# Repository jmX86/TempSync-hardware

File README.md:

# TempSync-hardware
Električne sheme i software za termostat

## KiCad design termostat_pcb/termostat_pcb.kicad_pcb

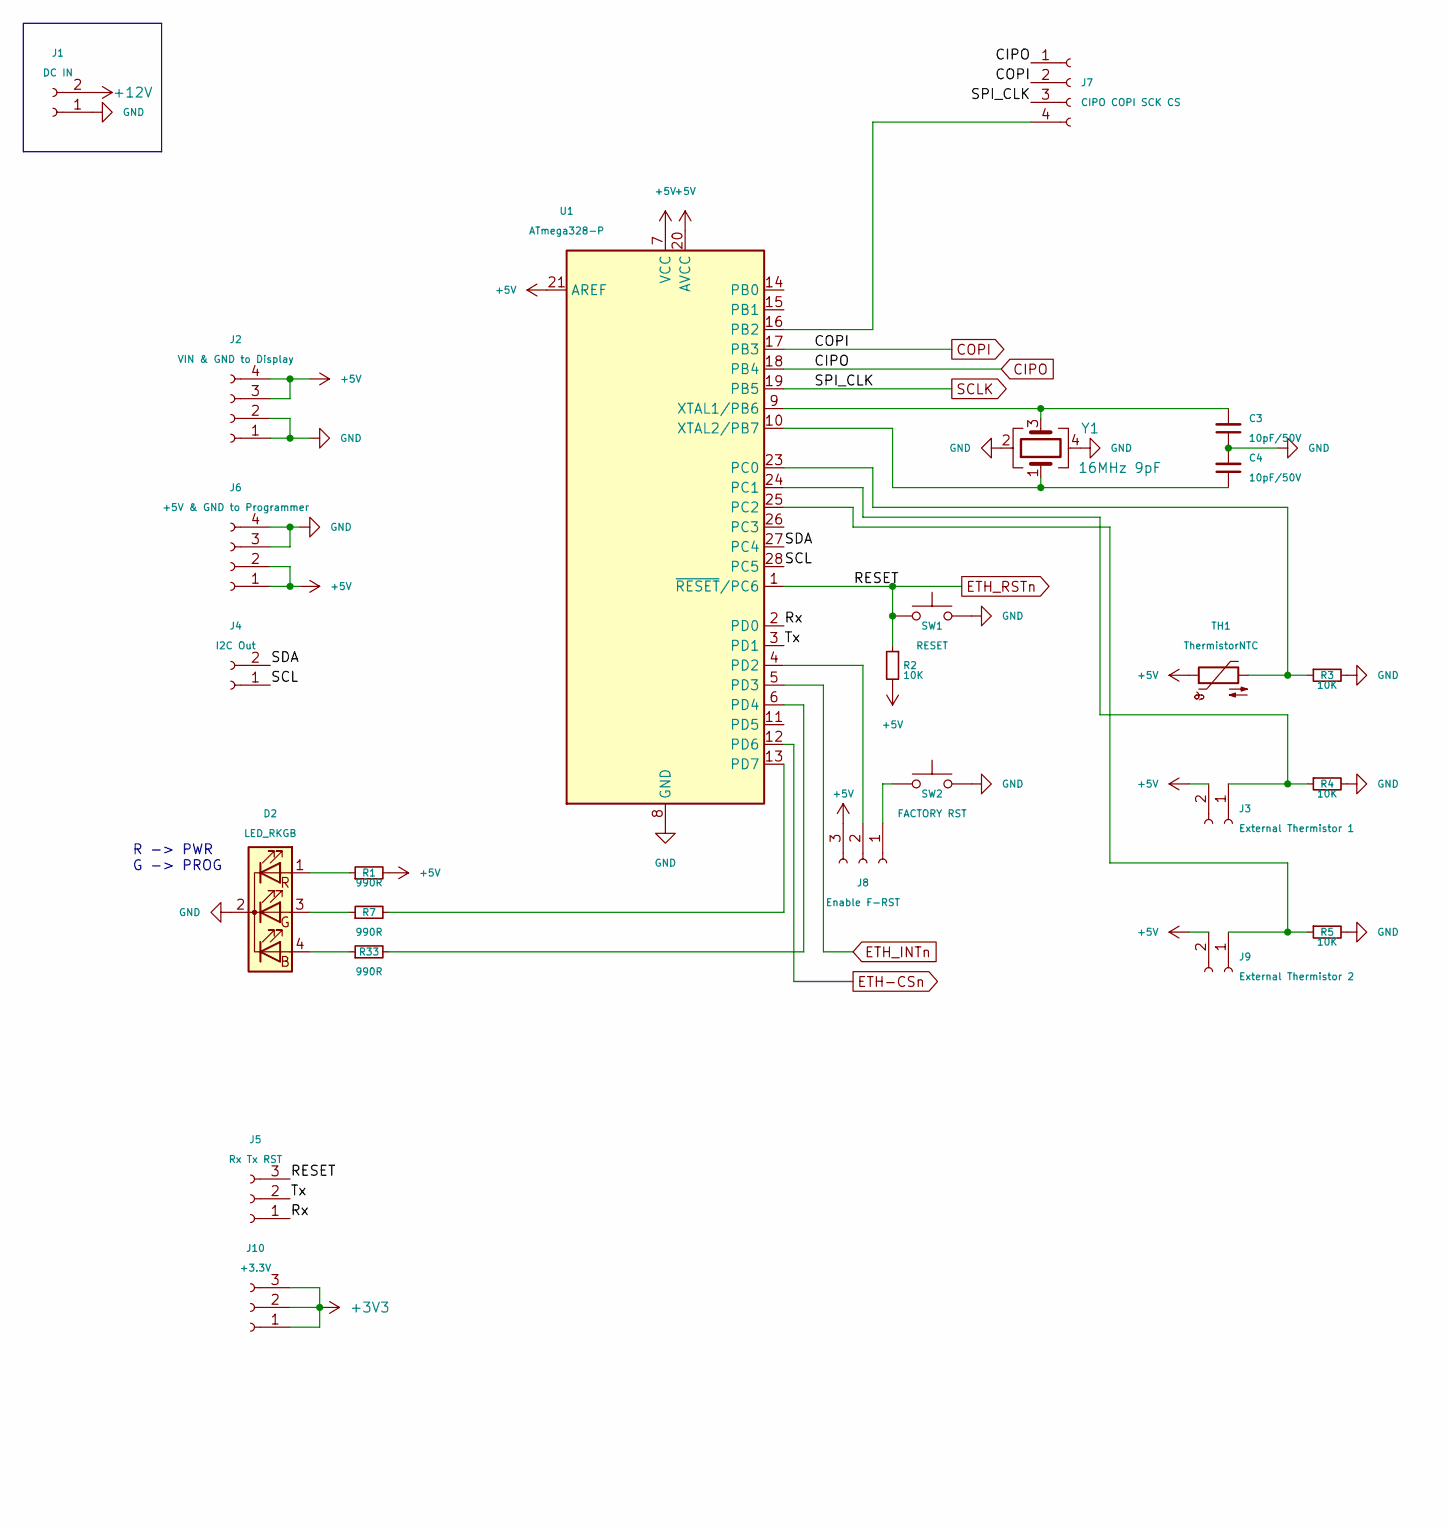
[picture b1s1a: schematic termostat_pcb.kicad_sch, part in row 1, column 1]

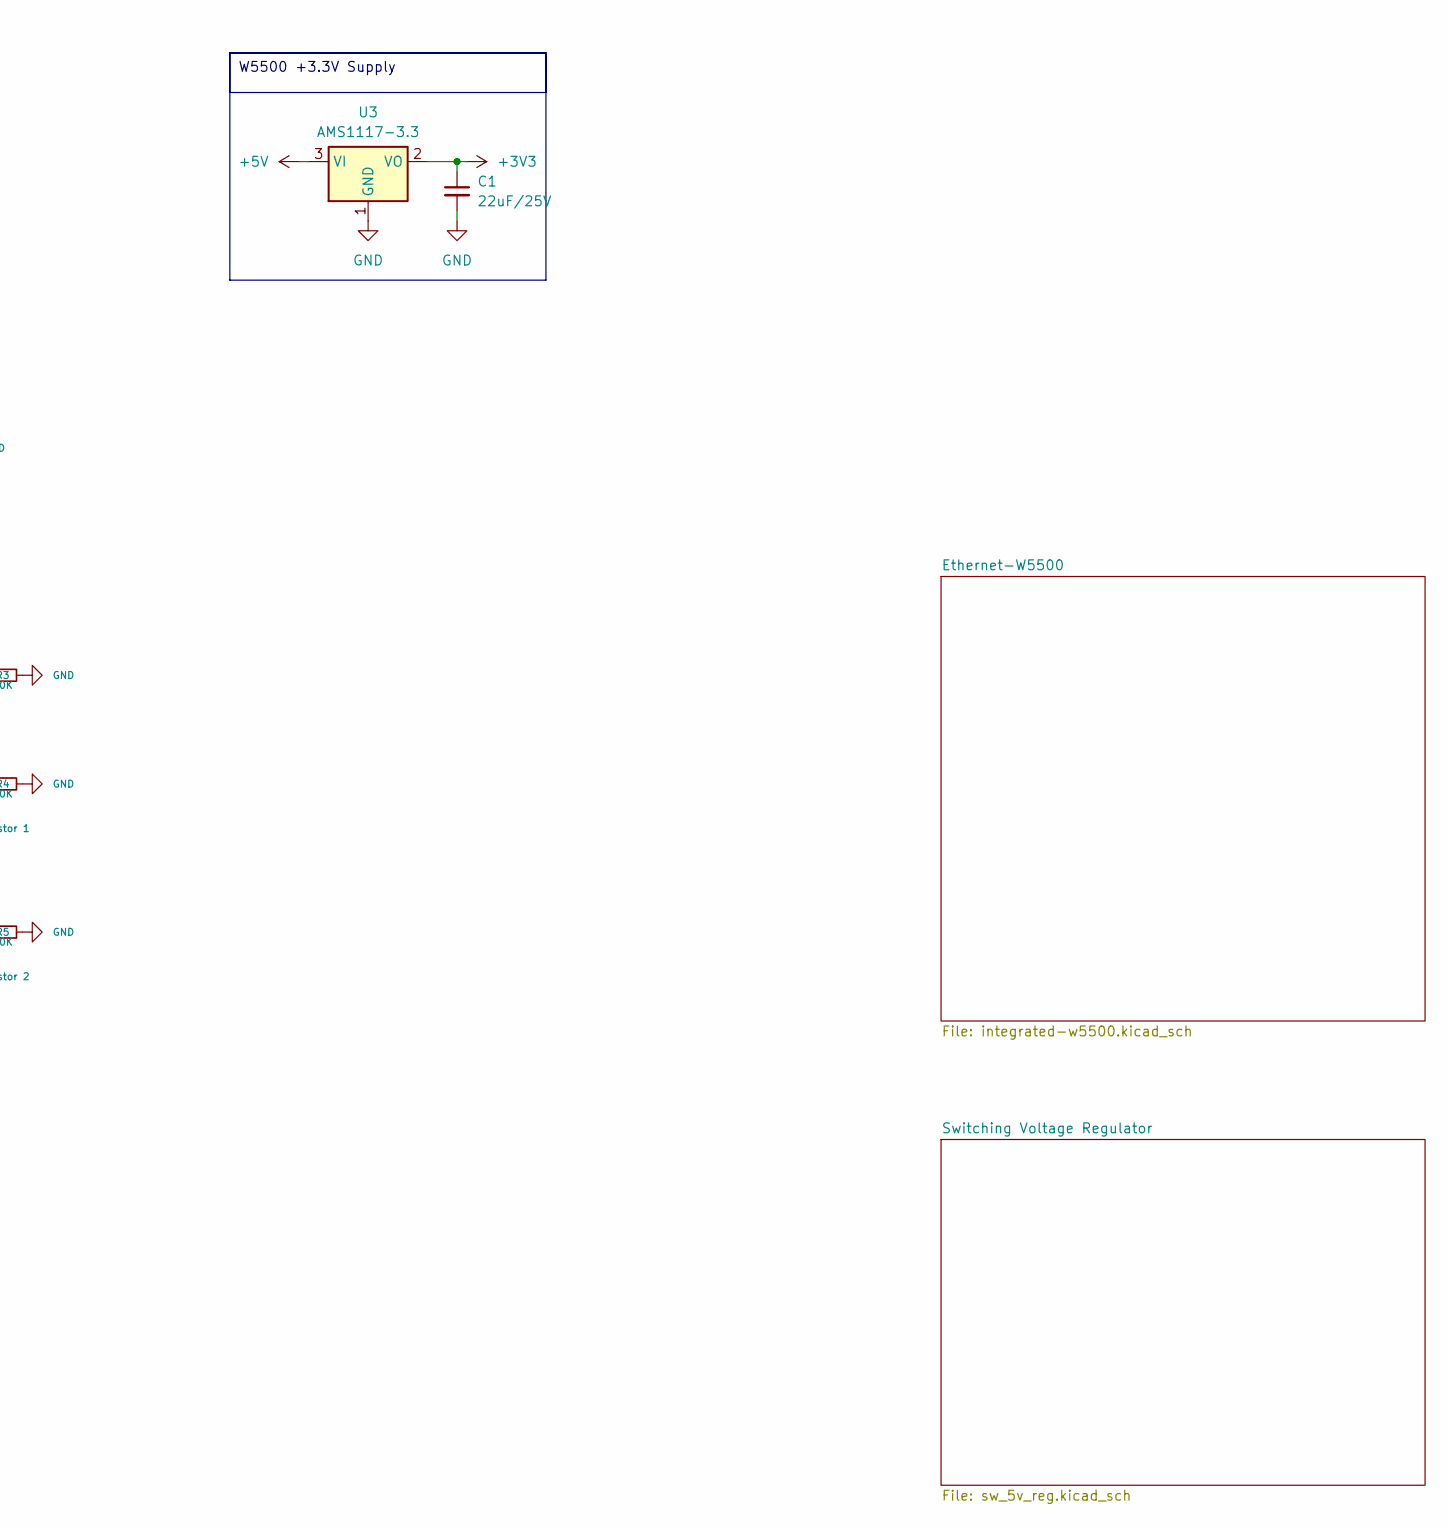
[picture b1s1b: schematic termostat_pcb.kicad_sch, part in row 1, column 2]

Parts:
C1: 22uF/25V; C_0805_2012Metric; LCSC C45783
C3, C4: 10pF/50V; C_0603_1608Metric; LCSC C1634
D2: LED_RKGB; LED_D5.0mm-4_RGB
J1: DC IN; PhoenixContact_MCV_1,5_2-G-5.08_1x02_P5.08mm_Vertical
J2: VIN & GND to Display; PinHeader_1x04_P2.54mm_Vertical
J3: External Thermistor 1; PhoenixContact_MCV_1,5_2-G-5.08_1x02_P5.08mm_Vertical
J4: I2C Out; PinHeader_1x02_P2.54mm_Vertical
J5: Rx Tx RST; PinHeader_1x03_P2.54mm_Vertical
J6: +5V & GND to Programmer; PinHeader_1x04_P2.54mm_Vertical
J7: CIPO COPI SCK CS; PinHeader_1x04_P2.54mm_Vertical
J8: Enable F-RST; PinHeader_1x03_P2.54mm_Vertical
J9: External Thermistor 2; PhoenixContact_MCV_1,5_2-G-5.08_1x02_P5.08mm_Vertical
J10: +3.3V; PinHeader_1x03_P2.54mm_Vertical
R1, R7, R33: 990R; R_Axial_DIN0207_L6.3mm_D2.5mm_P10.16mm_Horizontal
R2, R3, R4, R5: 10K; R_1206_3216Metric; LCSC C17902
SW1: RESET; SW_PUSH_6mm_H5mm
SW2: FACTORY RST; SW_PUSH_6mm_H5mm
TH1: ThermistorNTC; R_Axial_DIN0204_L3.6mm_D1.6mm_P1.90mm_Vertical
U1: ATmega328-P; DIP-28_W7.62mm
U3: AMS1117-3.3; SOT-223-3_TabPin2; LCSC C6186
Y1: 16MHz 9pF; Crystal_SMD_3225-4Pin_3.2x2.5mm; LCSC C13638

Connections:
+3V3: C1.1, J10.1, J10.2, J10.3, U3.2 (VO); also elsewhere on the board
+5V: J2.3, J2.4, J3.2, J6.1, J6.2, J8.3, J9.2, R1.2, R2.2, TH1.1, U1.7 (VCC), U1.20 (AVCC), U1.21 (AREF), U3.3 (VI); also elsewhere on the board
+12V: J1.2; also elsewhere on the board
/Rx: J5.1, U1.2 (PD0)
/SCL: J4.1, U1.28 (PC5)
/SDA: J4.2, U1.27 (PC4)
/Tx: J5.2, U1.3 (PD1)
CIPO: J7.1, U1.18 (PB4); also elsewhere on the board
COPI: J7.2, U1.17 (PB3); also elsewhere on the board
ETH-CSn: U1.12 (PD6); also elsewhere on the board
ETH_INTn: U1.5 (PD3); also elsewhere on the board
ETH_RSTn: J5.3, R2.1, SW1.1, U1.1 (~RESET/PC6); also elsewhere on the board
GND: C1.2, C3.1, C4.2, D2.2 (K), J1.1, J2.1, J2.2, J6.3, J6.4, R3.2, R4.2, R5.2, SW1.2, SW2.2, U1.8 (GND), U1.22 (GND), U3.1 (GND), Y1.2, Y1.4; also elsewhere on the board
unnamed: D2.4 (BA), R33.1
unnamed: D2.3 (GA), R7.1
unnamed: D2.1 (RA), R1.1
unnamed: J3.1, R4.1, U1.24 (PC1)
unnamed: J7.4, U1.16 (PB2)
unnamed: J8.1, SW2.1
unnamed: J8.2, U1.4 (PD2)
unnamed: J9.1, R5.1, U1.25 (PC2)
unnamed: R3.1, TH1.2, U1.23 (PC0)
unnamed: R33.2, U1.6 (PD4)
unnamed: R7.2, U1.13 (PD7)
unnamed: C3.2, U1.9 (XTAL1/PB6), Y1.3
unnamed: C4.1, U1.10 (XTAL2/PB7), Y1.1
SCLK: J7.3, U1.19 (PB5); also elsewhere on the board

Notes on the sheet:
W5500 +3.3V Supply
R -> PWR G -> PROG

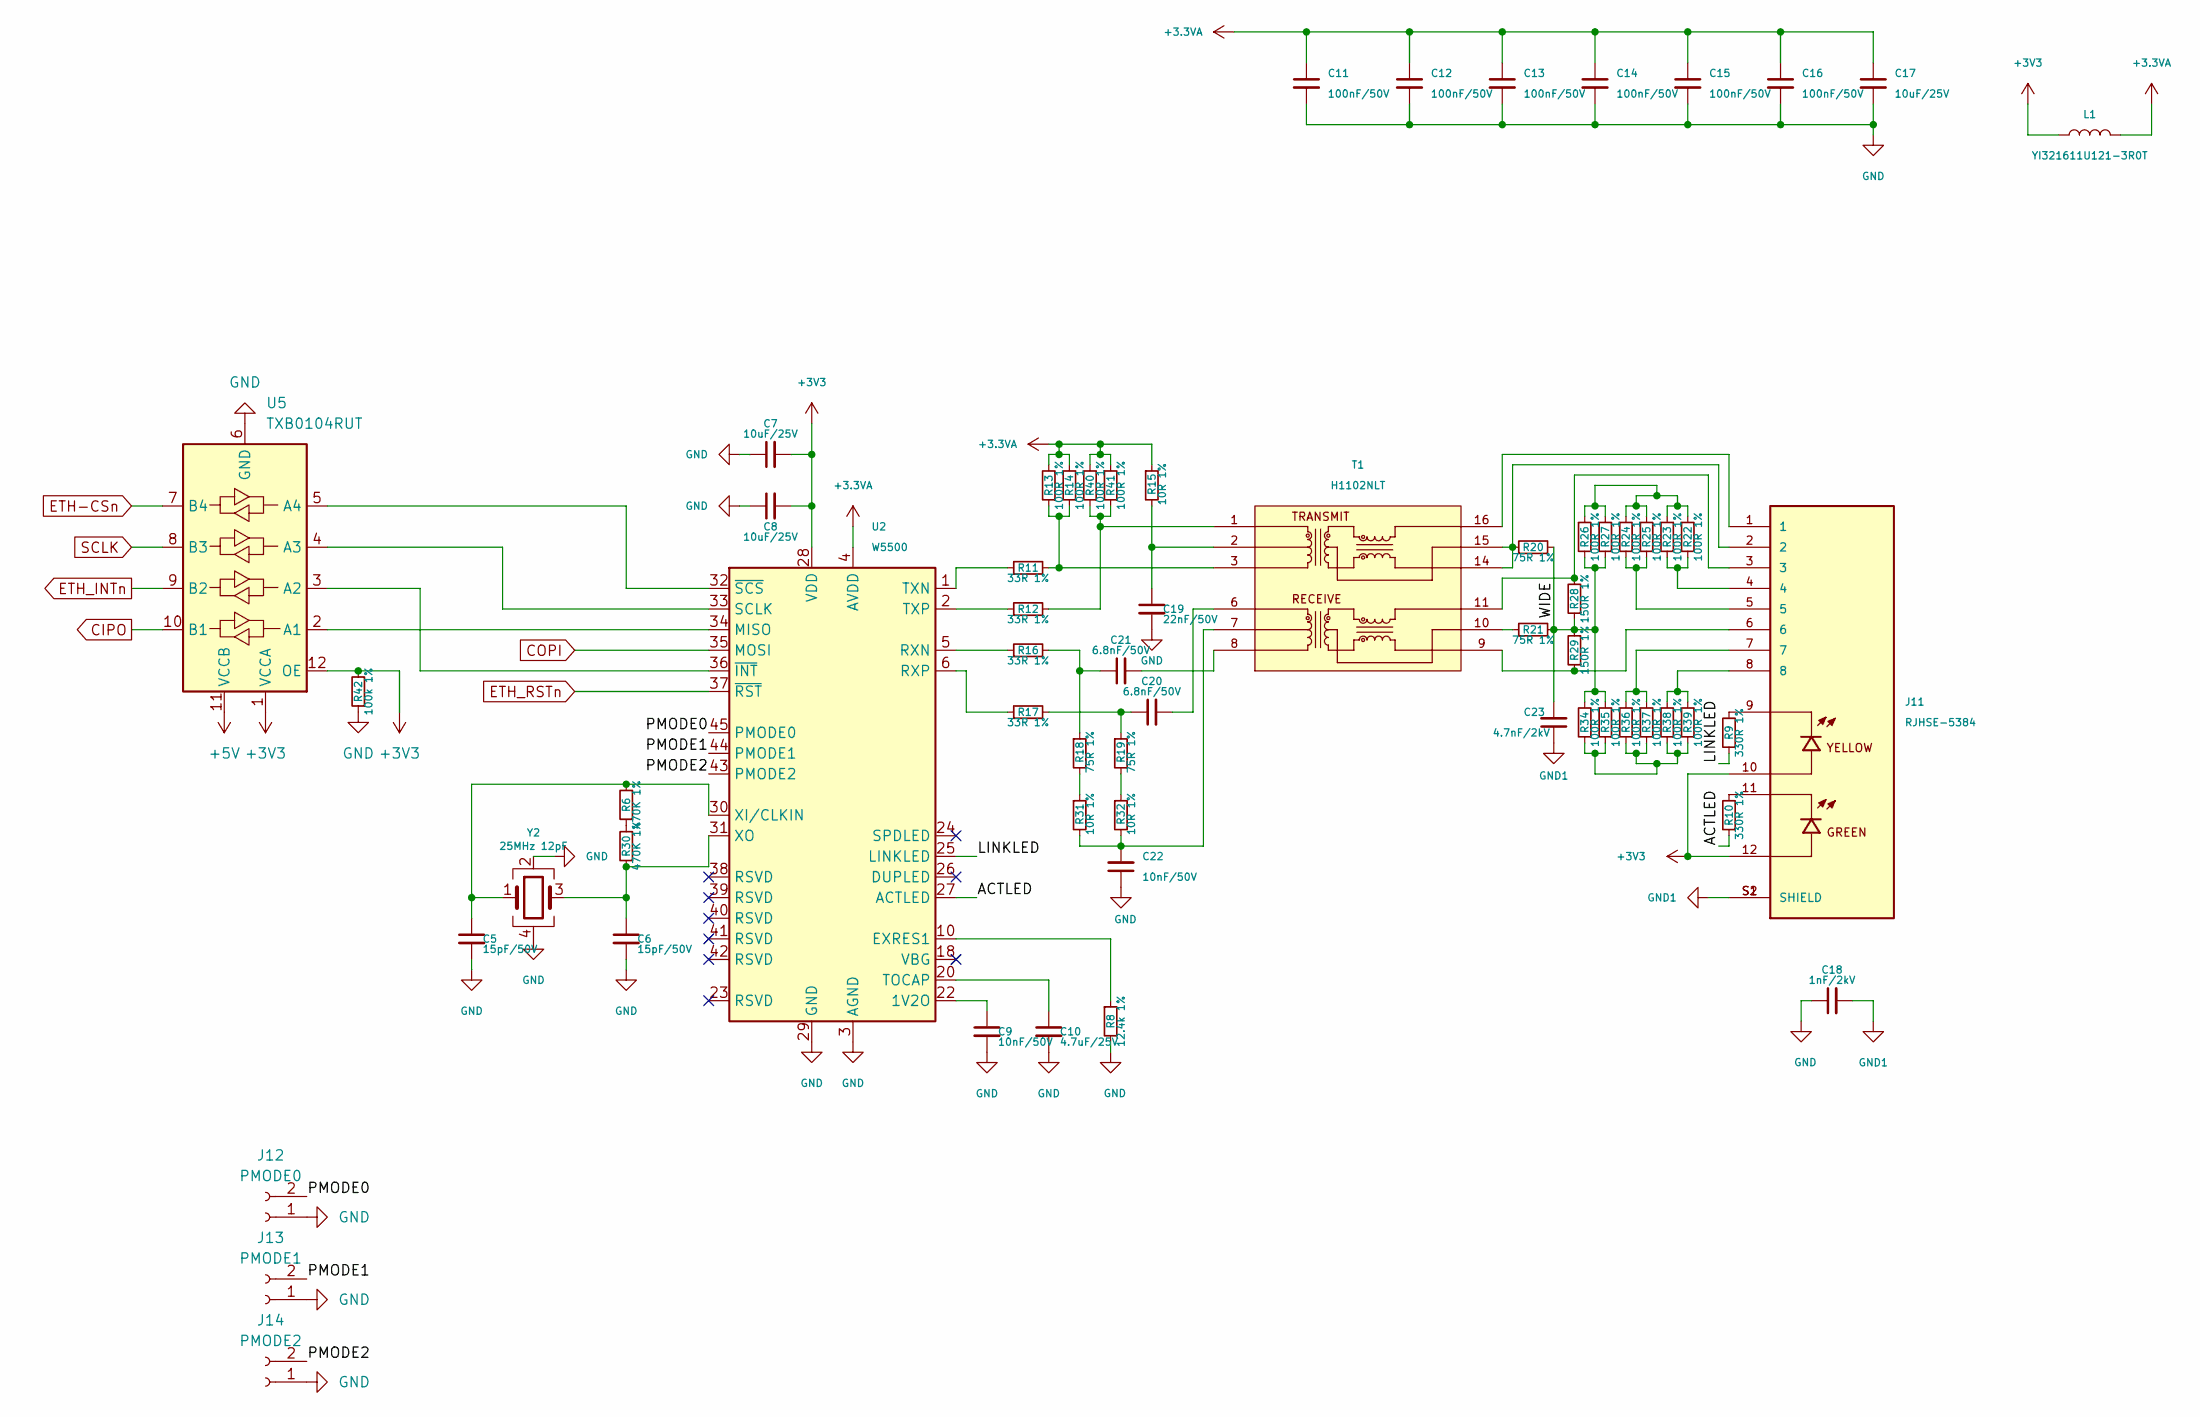
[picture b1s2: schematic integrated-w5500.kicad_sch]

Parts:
C5, C6: 15pF/50V; C_0603_1608Metric; LCSC C1644
C7, C8, C17: 10uF/25V; C_0805_2012Metric; LCSC C15850
C9, C22: 10nF/50V; C_0805_2012Metric; LCSC C1710
C10: 4.7uF/25V; C_0805_2012Metric; LCSC C1779
C11, C12, C13, C14, C15, C16: 100nF/50V; C_1206_3216Metric; LCSC C24497
C18: 1nF/2kV; C_1206_3216Metric; LCSC C9196
C19: 22nF/50V; C_0603_1608Metric; LCSC C21122
C20, C21: 6.8nF/50V; C_0603_1608Metric; LCSC C1631
C23: 4.7nF/2kV; C_1210_3225Metric; LCSC C427530
J11: RJHSE-5384; AMPHENOL_RJHSE-5384; PARTREV E; LCSC C464587
J12: PMODE0; PinHeader_1x02_P2.54mm_Vertical
J13: PMODE1; PinHeader_1x02_P2.54mm_Vertical
J14: PMODE2; PinHeader_1x02_P2.54mm_Vertical
L1: YI321611U121-3R0T; L_1206_3216Metric; LCSC C2858470
R6, R30: 470K 1%; R_0805_2012Metric; LCSC C17709
R8: 12.4k 1%; R_1206_3216Metric; LCSC C322840
R9, R10: 330R 1%; R_0805_2012Metric; LCSC C17630
R11, R12, R16, R17: 33R 1%; R_0805_2012Metric; LCSC C17634
R13, R14, R22, R23, R24, R25, R26, R27, R34, R35, R36, R37, R38, R39, R40, R41: 100R 1%; R_0805_2012Metric; LCSC C17408
R15, R31, R32: 10R 1%; R_1206_3216Metric; LCSC C17903
R18, R19, R20, R21: 75R 1%; R_0603_1608Metric; LCSC C4275
R28, R29: 150R 1%; R_0805_2012Metric; LCSC C17471
R42: 100k 1%; R_0603_1608Metric; LCSC C25803
T1: H1102NLT; XFMR_H1102NLT; PARTREV NA; LCSC C18584
U2: W5500; LQFP-48_7x7mm_P0.5mm; LCSC C32843
U5: TXB0104RUT; Texas_R-PUQFN-N12; LCSC C105266
Y2: 25MHz 12pF; Crystal_SMD_3225-4Pin_3.2x2.5mm; LCSC C9006

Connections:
+3.3VA: C11.1, C12.1, C13.1, C14.1, C15.1, C16.1, C17.1, L1.2, R13.2, R14.2, R15.1, R40.2, R41.2, U2.4 (AVDD), U2.8 (AVDD), U2.11 (AVDD), U2.15 (AVDD), U2.17 (AVDD), U2.21 (AVDD)
+3V3: C7.2, C8.2, J11.10, J11.12, L1.1, R42.2, U2.28 (VDD), U5.1 (VCCA), U5.12 (OE); also elsewhere on the board
+5V: U5.11 (VCCB); also elsewhere on the board
/Ethernet-W5500/ACTLED: R10.1, U2.27 (ACTLED)
/Ethernet-W5500/LINKLED: R9.1, U2.25 (LINKLED)
/Ethernet-W5500/PMODE0: J12.2, U2.45 (PMODE0)
/Ethernet-W5500/PMODE1: J13.2, U2.44 (PMODE1)
/Ethernet-W5500/PMODE2: J14.2, U2.43 (PMODE2)
/Ethernet-W5500/WIDE: C23.2, R20.2, R21.2, R26.1, R27.1, R28.1, R29.2, R34.2, R35.2
CIPO: U5.10 (B1); also elsewhere on the board
COPI: U2.35 (MOSI); also elsewhere on the board
ETH-CSn: U5.7 (B4); also elsewhere on the board
ETH_INTn: U5.9 (B2); also elsewhere on the board
ETH_RSTn: U2.37 (~RST); also elsewhere on the board
GND: C5.2, C6.2, C7.1, C8.1, C9.2, C10.2, C11.2, C12.2, C13.2, C14.2, C15.2, C16.2, C17.2, C18.1, C19.2, C22.1, J12.1, J13.1, J14.1, R8.2, R42.1, U2.3 (AGND), U2.9 (AGND), U2.14 (AGND), U2.16 (AGND), U2.19 (AGND), U2.29 (GND), U2.48 (AGND), U5.6 (GND), Y2.2, Y2.4; also elsewhere on the board
GND1: C18.2, C23.1, J11.S1 (SHIELD), J11.S2 (SHIELD)
unnamed: C19.1, R15.2, T1.2
unnamed: C20.1, R17.2, R19.1
unnamed: C20.2, T1.6
unnamed: C21.1, R16.2, R18.1
unnamed: C21.2, T1.8
unnamed: C22.2, R31.2, R32.2, T1.7
unnamed: J11.1, T1.16
unnamed: J11.2, R20.1, T1.14, T1.15
unnamed: J11.3, R28.2, T1.11
unnamed: J11.4, R22.1, R23.1
unnamed: J11.5, R24.1, R25.1
unnamed: J11.6, R29.1, T1.9
unnamed: J11.7, R36.2, R37.2
unnamed: J11.8, R38.2, R39.2
unnamed: J11.9, R9.2
unnamed: J11.11, R10.2
unnamed: R11.2, R13.1, R14.1, T1.3
unnamed: R12.2, R40.1, R41.1, T1.1
unnamed: R18.2, R31.1
unnamed: R19.2, R32.1
unnamed: R21.1, T1.10
unnamed: R22.2, R23.2, R24.2, R25.2, R26.2, R27.2
unnamed: R6.1, R30.2
unnamed: R34.1, R35.1, R36.1, R37.1, R38.1, R39.1
unnamed: C9.1, U2.22 (1V2O)
unnamed: R8.1, U2.10 (EXRES1)
unnamed: U2.34 (MISO), U5.2 (A1)
unnamed: R16.1, U2.5 (RXN)
unnamed: R17.1, U2.6 (RXP)
unnamed: U2.33 (SCLK), U5.4 (A3)
unnamed: C10.1, U2.20 (TOCAP)
unnamed: R11.1, U2.1 (TXN)
unnamed: R12.1, U2.2 (TXP)
unnamed: C5.1, R6.2, U2.30 (XI/CLKIN), Y2.1
unnamed: C6.1, R30.1, U2.31 (XO), Y2.3
unnamed: U2.36 (~INT), U5.3 (A2)
unnamed: U2.32 (~SCS), U5.5 (A4)
SCLK: U5.8 (B3); also elsewhere on the board

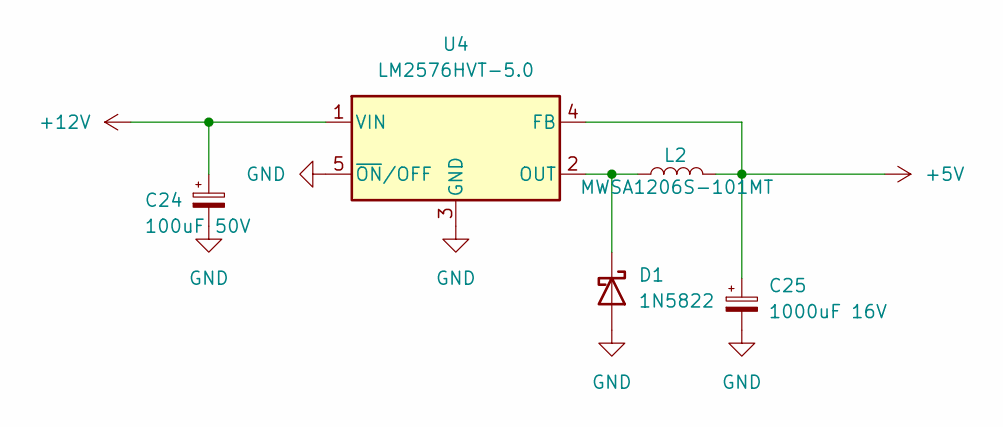
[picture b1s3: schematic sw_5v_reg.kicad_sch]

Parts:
C24: 100uF 50V; CP_Radial_D8.0mm_P3.50mm; LCSC C88728
C25: 1000uF 16V; C_Elec_10x10.2; LCSC C280408
D1: 1N5822; D_DO-201AD_P15.24mm_Horizontal; LCSC C84619
L2: MWSA1206S-101MT; L_Sunlord_MWSA1206S-101; LCSC C408533
U4: LM2576HVT-5.0; TO-220-5_Vertical; LCSC C434577

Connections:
+5V: C25.1, L2.2, U4.4 (FB); also elsewhere on the board
+12V: C24.1, U4.1 (VIN); also elsewhere on the board
GND: C24.2, C25.2, D1.2 (A), U4.3 (GND), U4.5 (~ON/OFF); also elsewhere on the board
unnamed: D1.1 (K), L2.1, U4.2 (OUT)

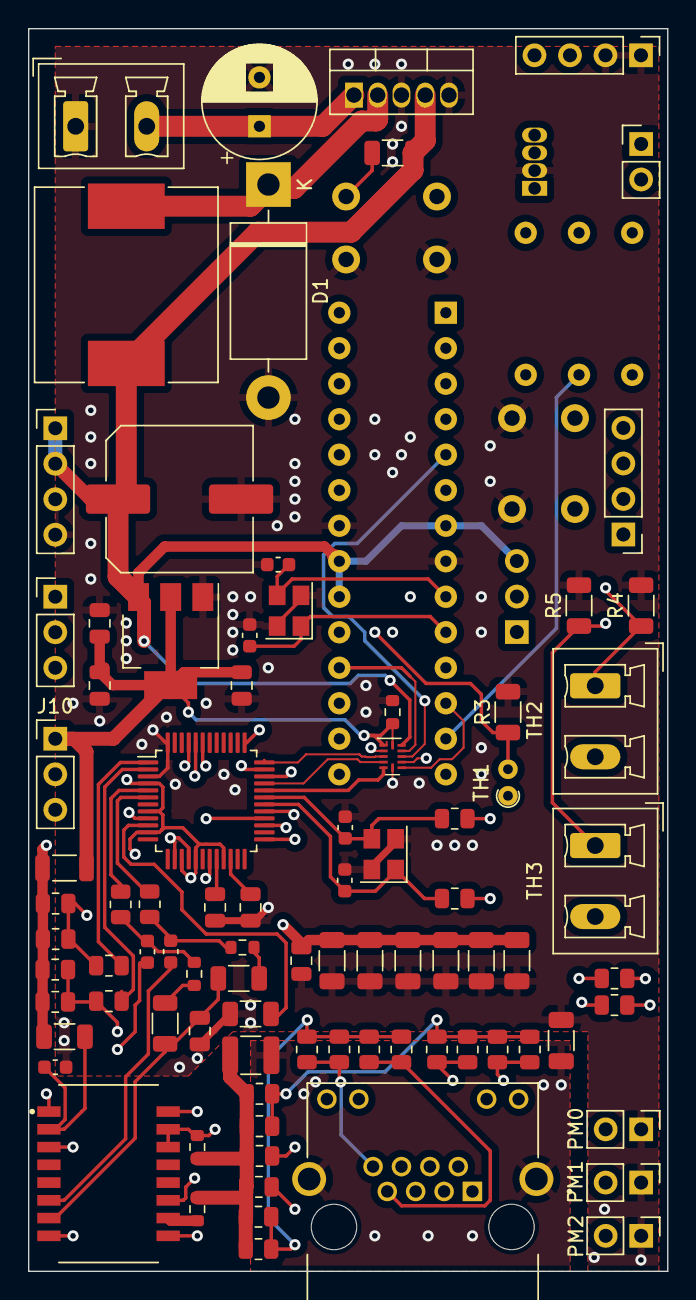
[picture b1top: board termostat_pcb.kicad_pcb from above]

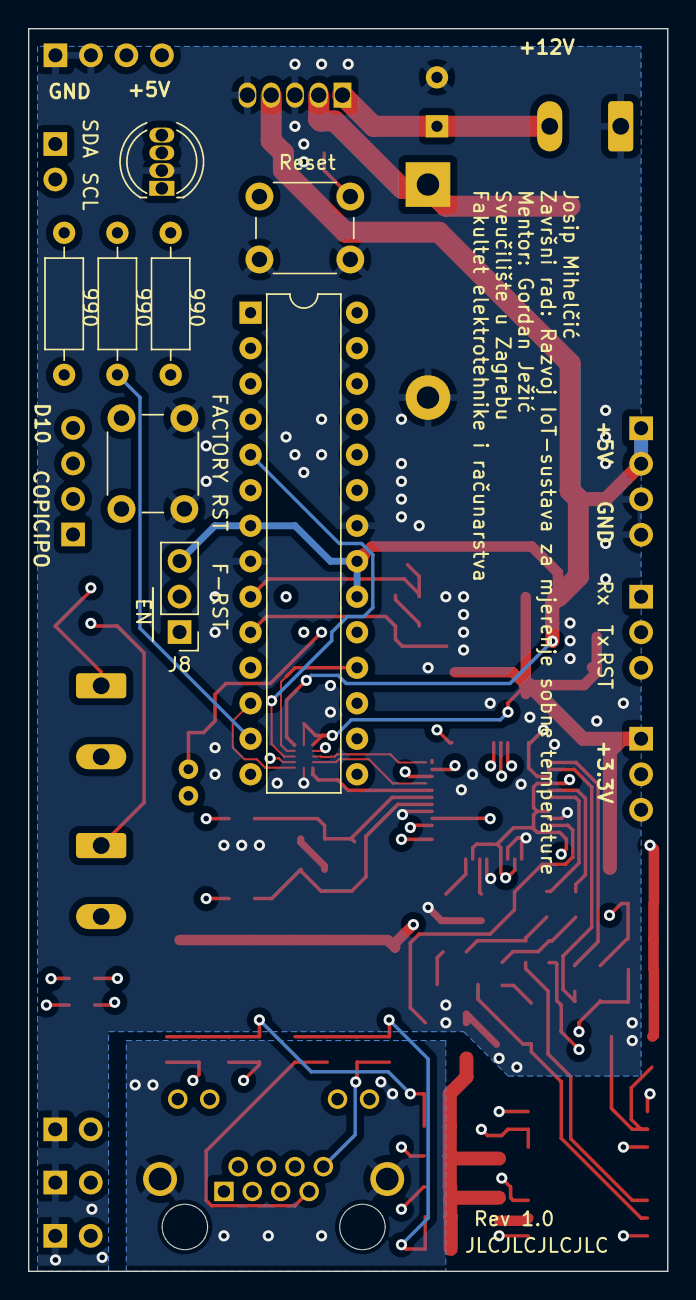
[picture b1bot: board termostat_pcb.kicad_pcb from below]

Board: 4 copper layers, 45.7 x 88.9 mm, 95 parts (8 on the bottom side), 73 nets.

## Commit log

2024-06-02 Termostat Rev 1.0
2024-06-03 EEPROM_reset and Termostat
2024-06-07 TermostatSetupApp
2024-06-07 Local Mosquitto Broker
